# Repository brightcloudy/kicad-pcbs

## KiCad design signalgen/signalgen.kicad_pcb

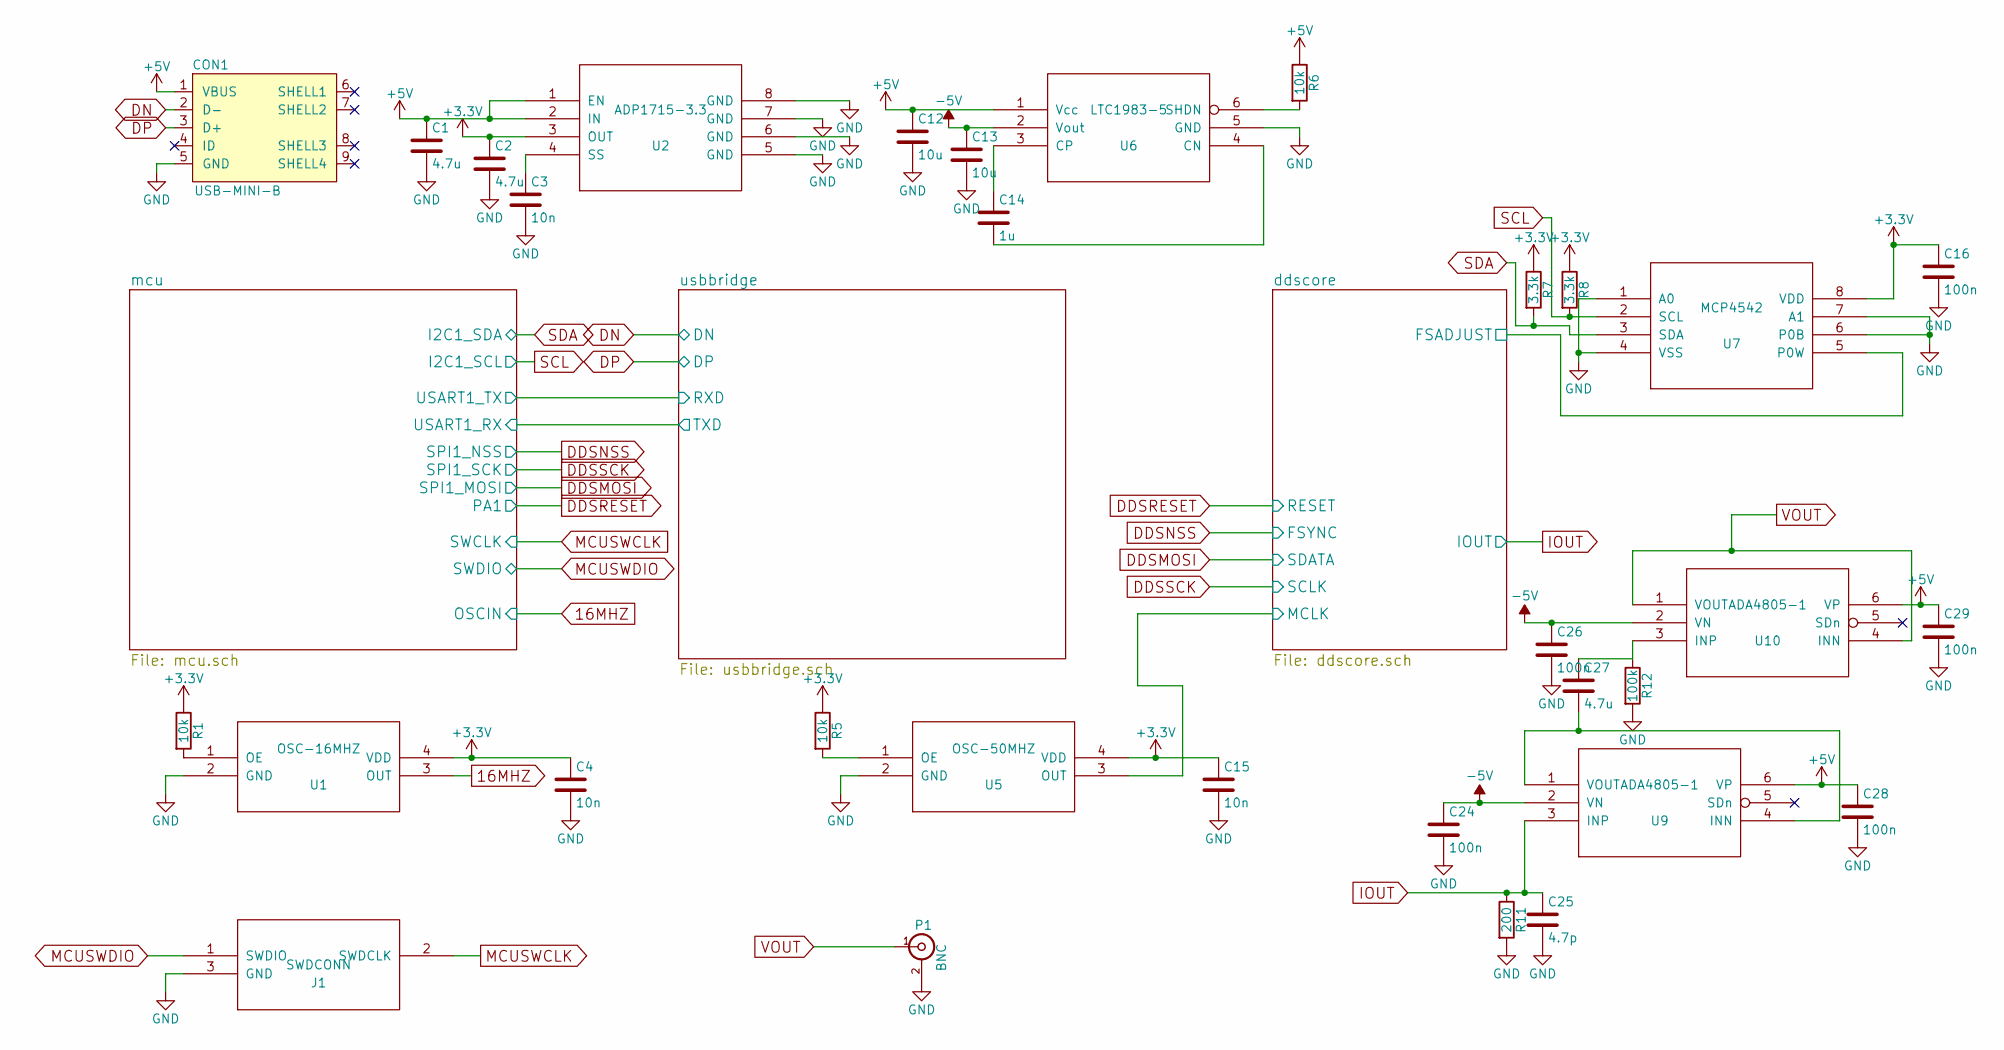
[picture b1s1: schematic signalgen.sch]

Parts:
C1, C2, C27: 4.7u; C_0603
C3, C4, C15: 10n; C_0402
C12, C13: 10u; C_0603
C14: 1u; C_0402
C16, C24, C26, C28, C29: 100n; C_0402
C25: 4.7p; C_0603
CON1: USB-MINI-B; USB_Mini-B
J1: SWDCONN; Pin_Header_Straight_1x03
P1: BNC; sma_straight_32k101-400l5
R1, R5, R6: 10k; R_0402
R7, R8: 3.3k; R_0402
R11: 200; R_0402
R12: 100k; R_0402
U1: OSC-16MHZ; SIOSC
U2: ADP1715-3.3; MSOP-8_3x3mm_Pitch0.65mm
U5: OSC-50MHZ; SIOSC
U6: LTC1983-5; SOT-23-6
U7: MCP4542; MSOP-8_3x3mm_Pitch0.65mm
U9, U10: ADA4805-1; SC-70-6

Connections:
16MHZ: U1.3 (OUT); also elsewhere on the board
+3V3: C2.1, C4.1, C15.1, C16.1, R1.1, R5.1, R7.1, R8.1, U1.4 (VDD), U2.3 (OUT), U5.4 (VDD), U7.8 (VDD); also elsewhere on the board
+5V: C1.1, C12.1, C28.1, C29.1, CON1.1 (VBUS), R6.1, U2.1 (EN), U2.2 (IN), U6.1 (Vcc), U9.6 (VP), U10.6 (VP); also elsewhere on the board
-5V: C13.1, C24.1, C26.1, U6.2 (Vout), U9.2 (VN), U10.2 (VN)
/ddscore/FSADJUST: U7.5 (P0W); also elsewhere on the board
/ddscore/MCLK: U5.3 (OUT); also elsewhere on the board
DN: CON1.2 (D-); also elsewhere on the board
DP: CON1.3 (D+); also elsewhere on the board
GND: C1.2, C2.2, C3.2, C4.2, C12.2, C13.2, C15.2, C16.2, C24.2, C25.2, C26.2, C28.2, C29.2, CON1.5 (GND), J1.3 (GND), P1.2 (Ext), R11.2, R12.2, U1.2 (GND), U2.5 (GND), U2.6 (GND), U2.7 (GND), U2.8 (GND), U5.2 (GND), U6.5 (GND), U7.1 (A0), U7.4 (VSS), U7.6 (P0B), U7.7 (A1); also elsewhere on the board
IOUT: C25.1, R11.1, U9.3 (INP); also elsewhere on the board
MCUSWCLK: J1.2 (SWDCLK); also elsewhere on the board
MCUSWDIO: J1.1 (SWDIO); also elsewhere on the board
unnamed: C3.1, U2.4 (SS)
unnamed: C14.1, U6.3 (CP)
unnamed: C14.2, U6.4 (CN)
unnamed: C27.1, R12.1, U10.3 (INP)
unnamed: C27.2, U9.1 (VOUT), U9.4 (INN)
unnamed: R1.2, U1.1 (OE)
unnamed: R5.2, U5.1 (OE)
unnamed: R6.2, U6.6 (SHDN)
SCL: R8.2, U7.2 (SCL); also elsewhere on the board
SDA: R7.2, U7.3 (SDA); also elsewhere on the board
VOUT: P1.1 (In), U10.1 (VOUT), U10.4 (INN)

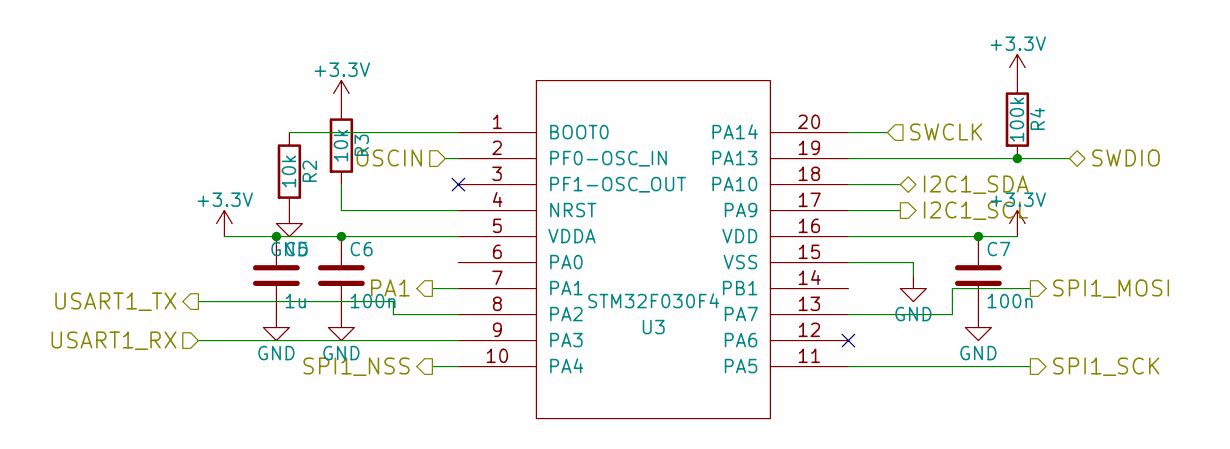
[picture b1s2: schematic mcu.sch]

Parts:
C5: 1u; C_0402
C6, C7: 100n; C_0402
R2, R3: 10k; R_0402
R4: 100k; R_0402
U3: STM32F030F4; TSSOP-20_4.4x6.5mm_Pitch0.65mm

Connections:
16MHZ: U3.2 (PF0-OSC_IN); also elsewhere on the board
+3V3: C5.1, C6.1, C7.1, R3.1, R4.1, U3.5 (VDDA), U3.16 (VDD); also elsewhere on the board
/usbbridge/RXD: U3.8 (PA2); also elsewhere on the board
/usbbridge/TXD: U3.9 (PA3); also elsewhere on the board
DDSMOSI: U3.13 (PA7); also elsewhere on the board
DDSNSS: U3.10 (PA4); also elsewhere on the board
DDSRESET: U3.7 (PA1); also elsewhere on the board
DDSSCK: U3.11 (PA5); also elsewhere on the board
GND: C5.2, C6.2, C7.2, R2.2, U3.15 (VSS); also elsewhere on the board
MCUSWCLK: U3.20 (PA14); also elsewhere on the board
MCUSWDIO: R4.2, U3.19 (PA13); also elsewhere on the board
unnamed: R2.1, U3.1 (BOOT0)
unnamed: R3.2, U3.4 (NRST)
SCL: U3.17 (PA9); also elsewhere on the board
SDA: U3.18 (PA10); also elsewhere on the board

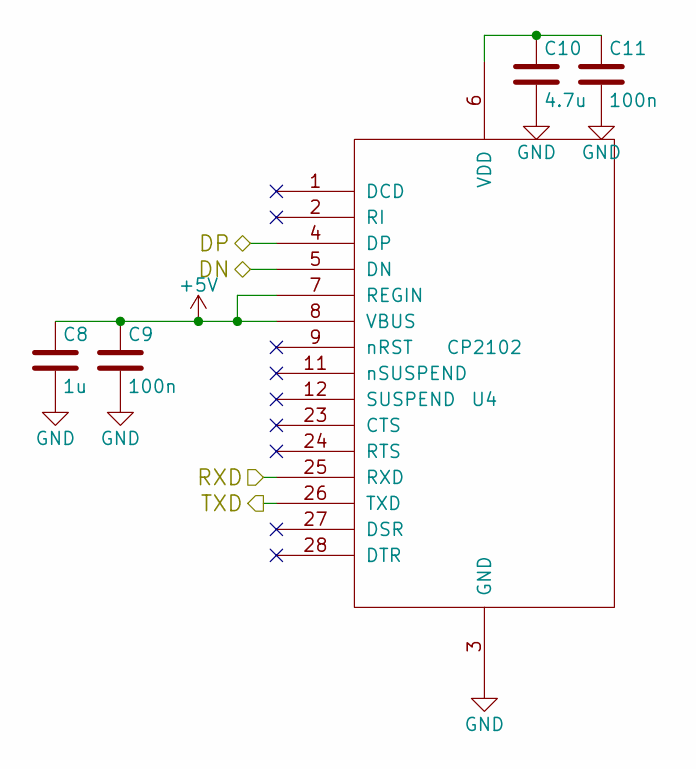
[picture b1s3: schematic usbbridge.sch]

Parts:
C8: 1u; C_0402
C9, C11: 100n; C_0402
C10: 4.7u; C_0603
U4: CP2102; QFN-28-1EP_5x5mm_Pitch0.5mm

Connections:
+5V: C8.1, C9.1, U4.7 (REGIN), U4.8 (VBUS); also elsewhere on the board
/usbbridge/RXD: U4.25 (RXD); also elsewhere on the board
/usbbridge/TXD: U4.26 (TXD); also elsewhere on the board
DN: U4.5 (DN); also elsewhere on the board
DP: U4.4 (DP); also elsewhere on the board
GND: C8.2, C9.2, C10.2, C11.2, U4.3 (GND); also elsewhere on the board
unnamed: C10.1, C11.1, U4.6 (VDD)

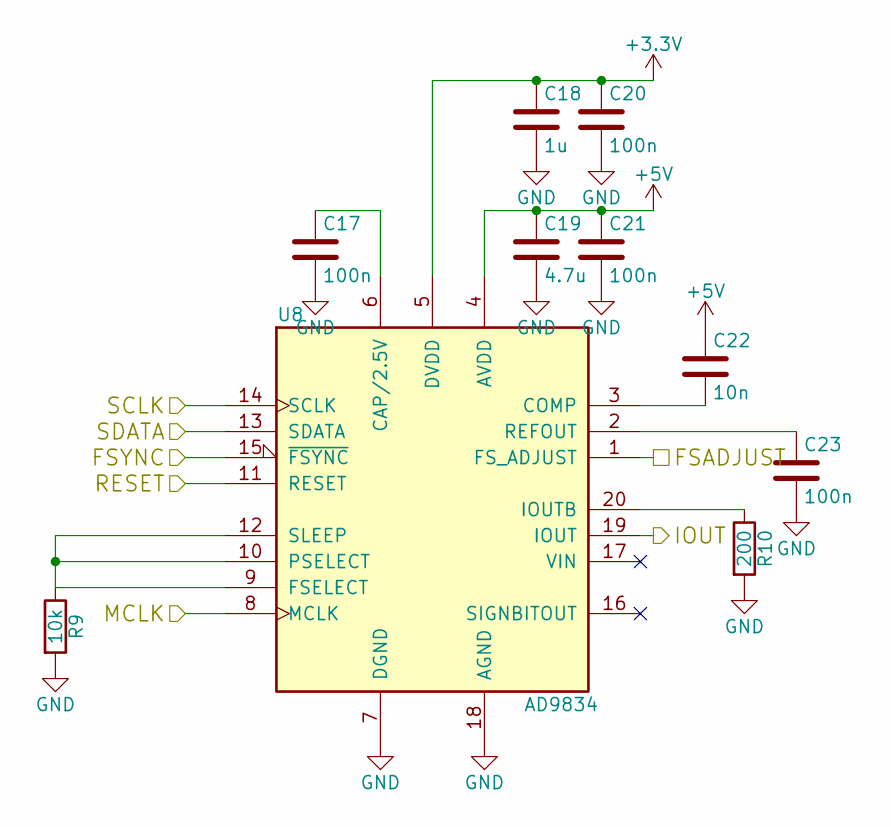
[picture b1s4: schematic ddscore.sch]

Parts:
C17, C20, C21, C23: 100n; C_0402
C18: 1u; C_0402
C19: 4.7u; C_0603
C22: 10n; C_0402
R9: 10k; R_0402
R10: 200; R_0402
U8: AD9834; TSSOP-20_4.4x6.5mm_Pitch0.65mm

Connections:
+3V3: C18.1, C20.1, U8.5 (DVDD); also elsewhere on the board
+5V: C19.1, C21.1, C22.1, U8.4 (AVDD); also elsewhere on the board
/ddscore/FSADJUST: U8.1 (FS_ADJUST); also elsewhere on the board
/ddscore/MCLK: U8.8 (MCLK); also elsewhere on the board
DDSMOSI: U8.13 (SDATA); also elsewhere on the board
DDSNSS: U8.15 (~FSYNC); also elsewhere on the board
DDSRESET: U8.11 (RESET); also elsewhere on the board
DDSSCK: U8.14 (SCLK); also elsewhere on the board
GND: C17.2, C18.2, C19.2, C20.2, C21.2, C23.2, R9.2, R10.2, U8.7 (DGND), U8.18 (AGND); also elsewhere on the board
IOUT: U8.19 (IOUT); also elsewhere on the board
unnamed: C17.1, U8.6 (CAP/2.5V)
unnamed: C22.2, U8.3 (COMP)
unnamed: C23.1, U8.2 (REFOUT)
unnamed: R9.1, U8.9 (FSELECT), U8.10 (PSELECT), U8.12 (SLEEP)
unnamed: R10.1, U8.20 (IOUTB)

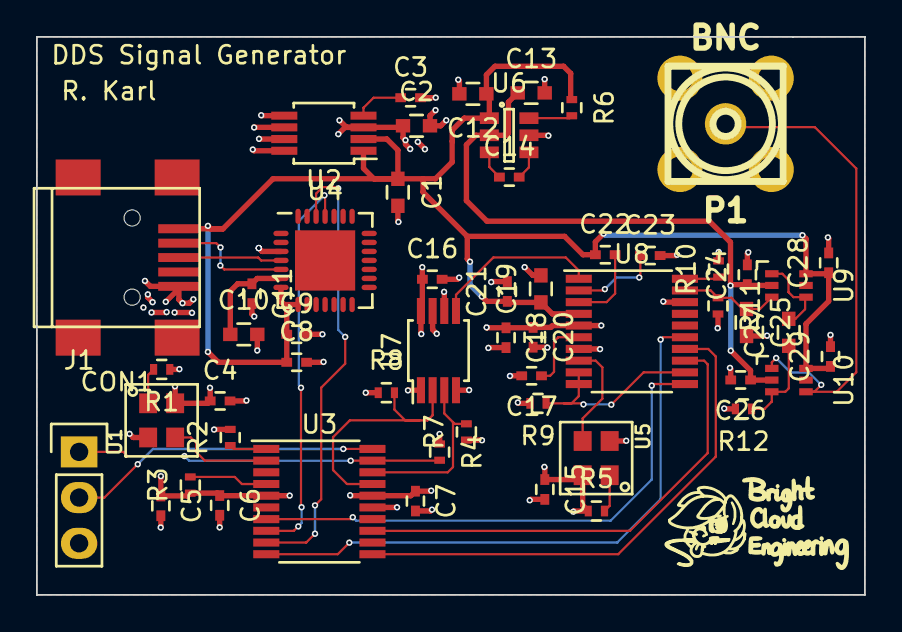
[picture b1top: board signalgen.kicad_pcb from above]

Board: 4 copper layers, 46.0 x 31.0 mm, 54 parts (0 on the bottom side), 37 nets.

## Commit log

2015-04-22 Initial commit & gerber processing shell scripts.
2015-04-22 Add DDS signal generator preliminary design document.
2015-04-23 First schematic for DDS Signal Generator with footprints associated.
2015-04-23 First layout of DDS signal generator.
